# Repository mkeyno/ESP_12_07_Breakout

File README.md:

# ESP_12_07_Breakout
this is breakout board for ESP module 12E, 12F &amp; 07, all pin breakout  except GIO03

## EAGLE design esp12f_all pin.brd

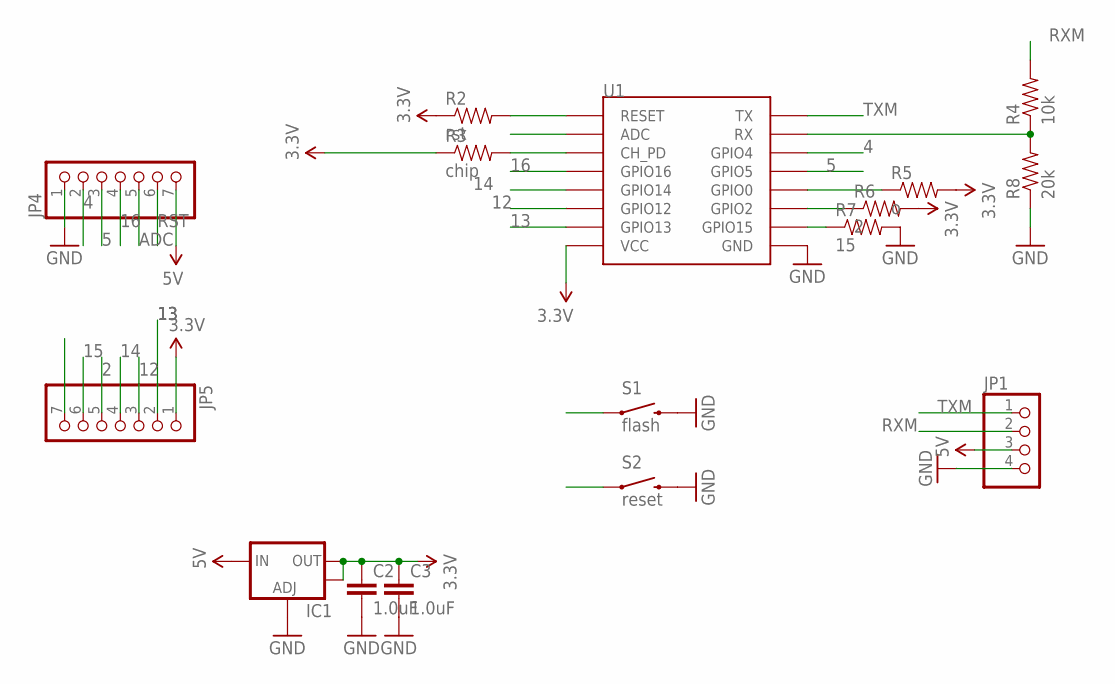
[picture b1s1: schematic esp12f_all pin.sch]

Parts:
C2, C3: 1.0uF; 1206
IC1: V_REG_LM1117SOT223; SOT223
JP1: PINHD-1X4; 1X04
JP4, JP5: PINHD-1X7; 1X07
R2: rst; 0805
R3: chip; 0805
R4: 10k; 0805
R5: o; 0805
R6: 2; 0805
R7: 15; 0805
R8: 20k; 0805
S1: flash; TACTILE-SWITCH-1101NE
S2: reset; TACTILE-SWITCH-1101NE
U1: ESP12SMD; ESP12-SMD

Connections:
0: JP5.7, R5.1, S1.1, U1.GPIO0
2: JP5.5, R6.1, U1.GPIO2
3.3V: C2.1, C3.1, IC1.2 (OUT), IC1.4 (OUT), JP5.1, R2.1, R3.1, R5.2, R6.2, U1.VCC
4: JP4.2, U1.GPIO4
5: JP4.3, U1.GPIO5
5V: IC1.3 (IN), JP1.3, JP4.7
12: JP5.3, U1.GPIO12
13: JP5.2, U1.GPIO13
14: JP5.4, U1.GPIO14
15: JP5.6, R7.1, U1.GPIO15
16: JP4.4, U1.GPIO16
ADC: JP4.5, U1.ADC
CH_PD: R3.2, U1.CH_PD
GND: C2.2, C3.2, IC1.1 (ADJ), JP1.4, JP4.1, R7.2, R8.1, S1.2, S2.2, U1.GND
unnamed: R4.1, R8.2, U1.RXD0 (RX)
RST: JP4.6, R2.2, S2.1, U1.RESET
RXM: JP1.2, R4.2
TXM: JP1.1, U1.TXD0 (TX)

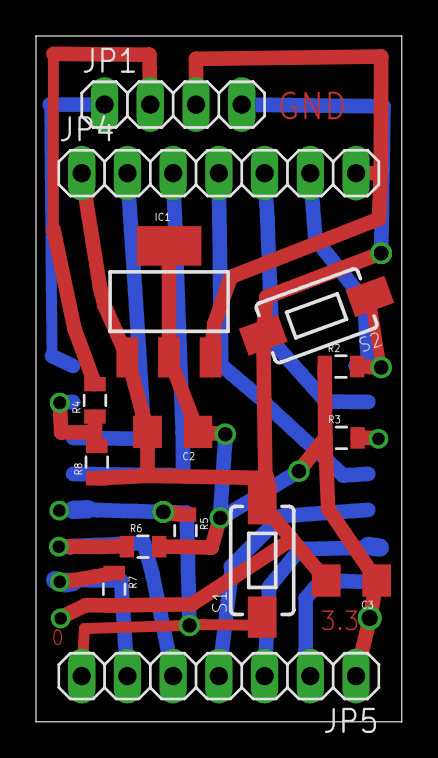
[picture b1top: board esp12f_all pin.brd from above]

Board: 2 copper layers, 20.3 x 38.1 mm, 16 parts (1 on the bottom side), 18 nets.

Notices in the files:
parts and their libraries:
SparkFun-Capacitors: Licensing: Creative Commons ShareAlike 4.0 International - https://creativecommons.org/licenses/by-sa/4.0
